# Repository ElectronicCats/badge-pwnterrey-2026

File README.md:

# Badge PWNTerrey

El **El Badge de Pwnterrey** es un dispositivo de hardware abierto y portátil diseñado para la auditoría de redes inalámbricas y seguridad de radiofrecuencia (WiFi, Bluetooth y NFC). Esta versión utiliza el potente y nuevo chip **ESP32-C5 (Arquitectura RISC-V)**, configurada específicamente para operar en modo **"Headless"** (sin pantalla), permitiendo la interacción total mediante consola serie (CLI) e integrando sensores y emuladores como NFC y GPS externo.

***

## 🚀 Características Principales

### 📶 Conectividad Inalámbrica Avanzada
- **Procesador ESP32-C5**: Chip de doble banda Wi-Fi 6 (2.4 GHz y 5 GHz) y Bluetooth 5 (LE) integrado.
- **Auditoría WiFi**: Soporte para escaneo de APs, rastreo de estaciones, sniffing de paquetes, inyección de tramas de desautenticación, spam de beacons y captura de handshakes.
- **Bluetooth (BLE)**: Capacidad para ejecutar ataques de spam BLE (`blespam`).

### 🏷️ Periféricos y Sensores Integrados
- **Emulador NFC (NT3H2111)**: Chip NTAG I2C 2k que permite actuar en **Modo Tarjeta**. El ESP32 emula una etiqueta pasiva para transferir datos NDEF (URLs, textos, vCards, redes WiFi) a teléfonos móviles o Flipper Zero.
- **Receptor GPS**: Interfaz serial dedicada para capturar coordenadas geográficas en tiempo real (Wardriving) y parsear sentencias NMEA.

### ⚙️ Optimización Headless (Sin Pantalla)
- **Bajo Consumo**: Al eliminar pantallas TFT/OLED y botones físicos, se reduce la huella energética y se maximiza la estabilidad.
- **Control Serial Total**: Una robusta interfaz de comandos (CLI) que permite controlar el 100% de las funciones del dispositivo.

***

## 📋 Especificaciones Técnicas

| Componente | Especificación |
| :--- | :--- |
| **Microcontrolador** | ESP32-C5 ECO1 (Arquitectura RISC-V de 32 bits) |
| **Wi-Fi** | Doble banda 2.4 GHz y 5 GHz (Wi-Fi 6 / 802.11ax) |
| **Bluetooth** | Bluetooth 5.0 (Low Energy - LE) |
| **NFC** | Chip **NT3H2111 (NTAG I2C 2k)** emulador de etiqueta pasiva |
| **GPS** | Interfaz serie dedicada para receptor GPS externo (UART1) |
| **Interfaz de Control**| CLI por Puerto Serie USB (115200 baudios) |
| **Estabilidad** | PSRAM desactivada, Flash configurada a 40MHz |

***

## 🔌 Interfaces y Pinout del ESP32-C5

El circuito integrado ESP32-C5 en su configuración Marauder utiliza los siguientes pines clave:

### 🌐 Conexión NFC (I2C)
El chip NTAG NT3H2111 está conectado a través del bus I2C:
- **SDA**: GPIO 2 (Pin 4)
- **SCL**: GPIO 3 (Pin 5)
- **Field Detect (FD)**: GPIO 6 (Pin 8) *(Detecta cuando un lector NFC externo energiza el campo inductivo)*

### 🛰️ Conexión GPS (UART1)
La comunicación con el módulo GPS se realiza mediante los pines:
- **GPS TX (MCU)**: GPIO 4 *(Hacia el pin RX del GPS)*
- **GPS RX (MCU)**: GPIO 5 *(Desde el pin TX del GPS)*
- **GPS ON/Power**: GPIO 7 *(Control de encendido del módulo GPS)*

***

## ⚡ Primeros Pasos

### 1. Alimentación y Conexión
Puedes alimentar y controlar tu adaptador de dos formas:
- **Conexión Directa USB**: Conéctalo a tu computadora usando un cable USB-C. El puerto creará un puerto COM serial.
- **Integración con Flipper Zero**: Conectado como un Addon GPIO al Flipper Zero, alimentado directamente desde los pines de 3.3V/5V del Flipper y controlado desde su aplicación de terminal.

### 2. Abrir la Terminal Serial
El dispositivo se comunica a **115200 baudios**, sin control de flujo (8N1).

#### 🐧 Linux / macOS
Usa el comando `screen` o `minicom`. Primero identifica el puerto (`/dev/ttyUSBX` o `/dev/ttyACM0`):
```bash
# Con screen (para salir: Ctrl+A, luego K)
screen /dev/ttyUSB0 115200

# Con minicom
sudo minicom -b 115200 -D /dev/ttyUSB0
```

#### 🪟 Windows
Usa clientes como **PuTTY** o **TeraTerm**:
- **Puerto**: COMx (Ver en administrador de dispositivos)
- **Baudrate**: 115200
- **Data bits**: 8
- **Parity**: None
- **Stop bits**: 1
- **Flow control**: None

***

## 🏷️ Control del Emulador NFC

El módulo NFC funciona exclusivamente en **modo emulación de etiqueta (Tag)**. No es un lector; actúa como una tarjeta inteligente pasiva que almacena registros NDEF.

### 🔍 Diagnóstico e Información
- **Escanear bus NFC**:
  ```bash
  nfc scan
  ```
  Realiza un escaneo de hardware (discovery) en los pares de pines del bus I2C para verificar la dirección del chip (`0x55` o `0x2A`).
- **Leer contenido actual de la etiqueta**:
  ```bash
  nfc read
  ```
  Muestra en hexadecimal y ASCII los bloques del 1 al 8 grabados en la memoria del chip NFC.

### ✍️ Escritura de Registros NDEF
Puedes programar el emulador NFC para inyectar diferentes cargas útiles:

- **🔗 Enlace Web (URL)**:
  ```bash
  nfc -u https://electroniccats.com
  ```
- **📝 Texto Plano**:
  ```bash
  nfc -t "Hola Hackers del ESP32-C5"
  ```
- **📇 Tarjeta de Contacto (vCard)**:
  ```bash
  nfc -v "Nombre,Telefono,Email"
  # Ejemplo:
  nfc -v "Electronic Cats,5551234567,info@electroniccats.com"
  ```
- **📶 Credenciales de Red WiFi**:
  ```bash
  nfc -w "SSID,Password,Autenticacion"
  # Ejemplo:
  nfc -w "MiRedSegura,Clave1234,WPA2"
  ```

Una vez ejecutado el comando con éxito, cualquier dispositivo móvil o lector NFC (como un Flipper Zero) que se acerque al sensor detectará la etiqueta y ejecutará la acción (abrir el link, importar el contacto o conectarse al WiFi).

***

## ⚙️ Configuración y Compilación de Firmware

Si deseas compilar o realizar modificaciones en el firmware, debes seguir estas recomendaciones específicas para el hardware ESP32-C5:

Clonar el [repositorio](https://github.com/ElectronicCats/badge-pwnterrey-2026)

### 🛠️ Configuración en configs.h
Asegúrate de que en el archivo [configs.h](file:///run/media/omaro/8C96D9BF96D9AA4A/ESP32Marauder/ESP32Marauder/esp32_marauder/configs.h) la definición activa para la placa sea:
```cpp
#define MARAUDER_FLIPPER_C5
```
Esta definición configurará automáticamente la ausencia de pantalla (`TFT_CS -1`), habilitará `HAS_BT`, `HAS_GPS` y `HAS_NFC` con sus respectivos mapeos de pines.

### ⚠️ Parámetros de Compilación en Arduino IDE
Debido al estado actual del soporte del chip, aplica las siguientes configuraciones de carga:
- **Placa**: ESP32C5 Dev Module
- **Arquitectura**: RISC-V (Compiler optimization)
- **Flash Frequency**: **40MHz** (Recomendado para máxima estabilidad)
- **Partition Scheme**: Minimal SPIFFS / No OTA (Para maximizar el espacio de programa y SPIFFS)
- **PSRAM**: Desactivada (Disabled)
- **Modo de Carga**: Inserte el dispositivo en modo Bootloader manteniendo presionado el botón Boot mientras conecta el USB si no es detectado automáticamente.

***

## ⌨️ Consola de Comandos Completa (CLI Reference)

A continuación se detalla la lista de comandos disponibles en el intérprete de comandos serial:

### 🛠️ Comandos de Administración

| Comando | Sintaxis | Descripción |
| :--- | :--- | :--- |
| `help` | `help` | Muestra la lista de comandos con su formato de ayuda. |
| `info` | `info` | Muestra información del sistema, compilación y hardware. |
| `reboot` | `reboot` | Reinicia el microcontrolador. |
| `channel` | `channel [-s <canal>]` | Muestra o cambia el canal WiFi activo. |
| `settings` | `settings [-s <setting> <enable/disable>]` | Muestra, modifica o reinicia (`-r`) los ajustes internos. |
| `spiffs` | `spiffs [ls / read <file> / rm <file> / format]`| Administra la memoria flash interna (SPIFFS). |
| `led` | `led -s <hex color> / -p <rainbow>` | Cambia el color del led de estado. |

### 📶 Auditoría WiFi (Sniffing & Scanning)

| Comando | Sintaxis | Descripción |
| :--- | :--- | :--- |
| `scanap` | `scanap` | Busca puntos de acceso (APs) inalámbricos cercanos. |
| `scansta` | `scansta` | Busca estaciones y clientes conectados. |
| `stopscan` | `stopscan` | Detiene inmediatamente cualquier escaneo en curso. |
| `list` | `list [-a / -s / -c / -t]` | Muestra listas cargadas (`-a` APs, `-s` SSIDs, `-c` Clientes). |
| `select` | `select -a/-s/-c <indices>` | Selecciona elementos por índice para interactuar. |
| `clearlist`| `clearlist -a/-c/-s` | Limpia los registros de la memoria RAM. |
| `ssid` | `ssid -a [-g <count> / -n <name>]` | Agrega SSIDs a la lista (`-g` aleatorios, `-n` específicos). |
| `sniffraw` | `sniffraw` | Captura y vuelca todos los paquetes raw recibidos. |
| `sniffbeacon`| `sniffbeacon` | Captura tramas beacon. |
| `sniffprobe`| `sniffprobe` | Captura peticiones probe request de clientes. |
| `sniffpwn` | `sniffpwn` | Sniffer enfocado en capturas de handshakes WPA. |
| `sniffpmkid`| `sniffpmkid [-c <channel>]` | Captura asociaciones PMKID para auditoría WPA2. |

### 💥 Comandos de Ataque WiFi y Bluetooth

| Comando | Sintaxis | Descripción |
| :--- | :--- | :--- |
| `attack` | `attack -t <deauth/beacon/probe/rickroll>` | Inicia ataque de desautenticación, spam de beacons, etc. |
| `blespam` | `blespam -t <apple/google/samsung/windows/all>`| Inicia campañas de spam publicitario Bluetooth BLE. |
| `wardrive` | `wardrive [-s]` | Inicia el modo Wardriving clásico sincronizado con GPS. |

***

## ⚠️ Advertencia de Seguridad

Esta herramienta ha sido diseñada exclusivamente para **fines educativos, pruebas de penetración ética y auditorías de seguridad autorizadas**. 

El uso de este dispositivo para interferir, interceptar o atacar redes e infraestructura ajena sin el consentimiento previo por escrito del propietario es **estrictamente ilegal**. Los desarrolladores y colaboradores no se hacen responsables del uso indebido de esta herramienta ni de los daños que este pueda causar.

## 📖 Documentación Adicional

- [Marauder App](https://github.com/ElectronicCats/marauder-ui-android-app)
- [Marauder UI Pro](https://github.com/ElectronicCats/marauder-ui-pro)
- [Firmware](https://github.com/ElectronicCats/pwnterrey-2026_Firmware)

## 🤝 Contribuciones

Este es un proyecto de hardware abierto. Las contribuciones son bienvenidas:

1. Haz un fork del repositorio.
2. Crea una nueva rama para tu feature (`git checkout -b feature/AmazingFeature`)
3. Haz commit de tus cambios (`git commit -m 'Add some AmazingFeature'`)
4. Haz push a tu rama (`git push origin feature/AmazingFeature`)
5. Abre un Pull Request

## 📝 Licencia

Este proyecto es de hardware abierto. Consulta los archivos de licencia para más detalles.

## 🏢 Electronic Cats

Desarollado con ❤️ por [Electronic Cats](https://www.electroniccats.com/)

Electronic Cats invierte tiempo y recursos en proporcionar este diseño de hardware abierto.
Por favor, apoya a Electronic Cats y al hardware abierto comprando productos de Electronic Cats.

## 📞 Contacto y soporte 

- **Website**: [https://www.electroniccats.com/](https://www.electroniccats.com/)
- **GitHub**: [ElectronicCats](https://github.com/ElectronicCats)
- **Issues**: Usa la sección de Issues en GitHub para reportar problemas o sugerir mejoras

## 🙏 Agradecimientos

Gracias a toda la comunidad de hardware abierto y a todas las personas que hacen posibles proyectos como este.

## 🤝 Credits & Ecosystem
- **Hardware & Support**: [Electronic Cats](https://electroniccats.com) 😼
- **Original Firmware**: [justcallmekoko](https://github.com/justcallmekoko)
- **UI Maintenance**: [michelangelomo](https://github.com/michelangelomo) & [Mikystars](https://github.com/Mikystars)

---
*Developed for the Offensive Security community.* 💀

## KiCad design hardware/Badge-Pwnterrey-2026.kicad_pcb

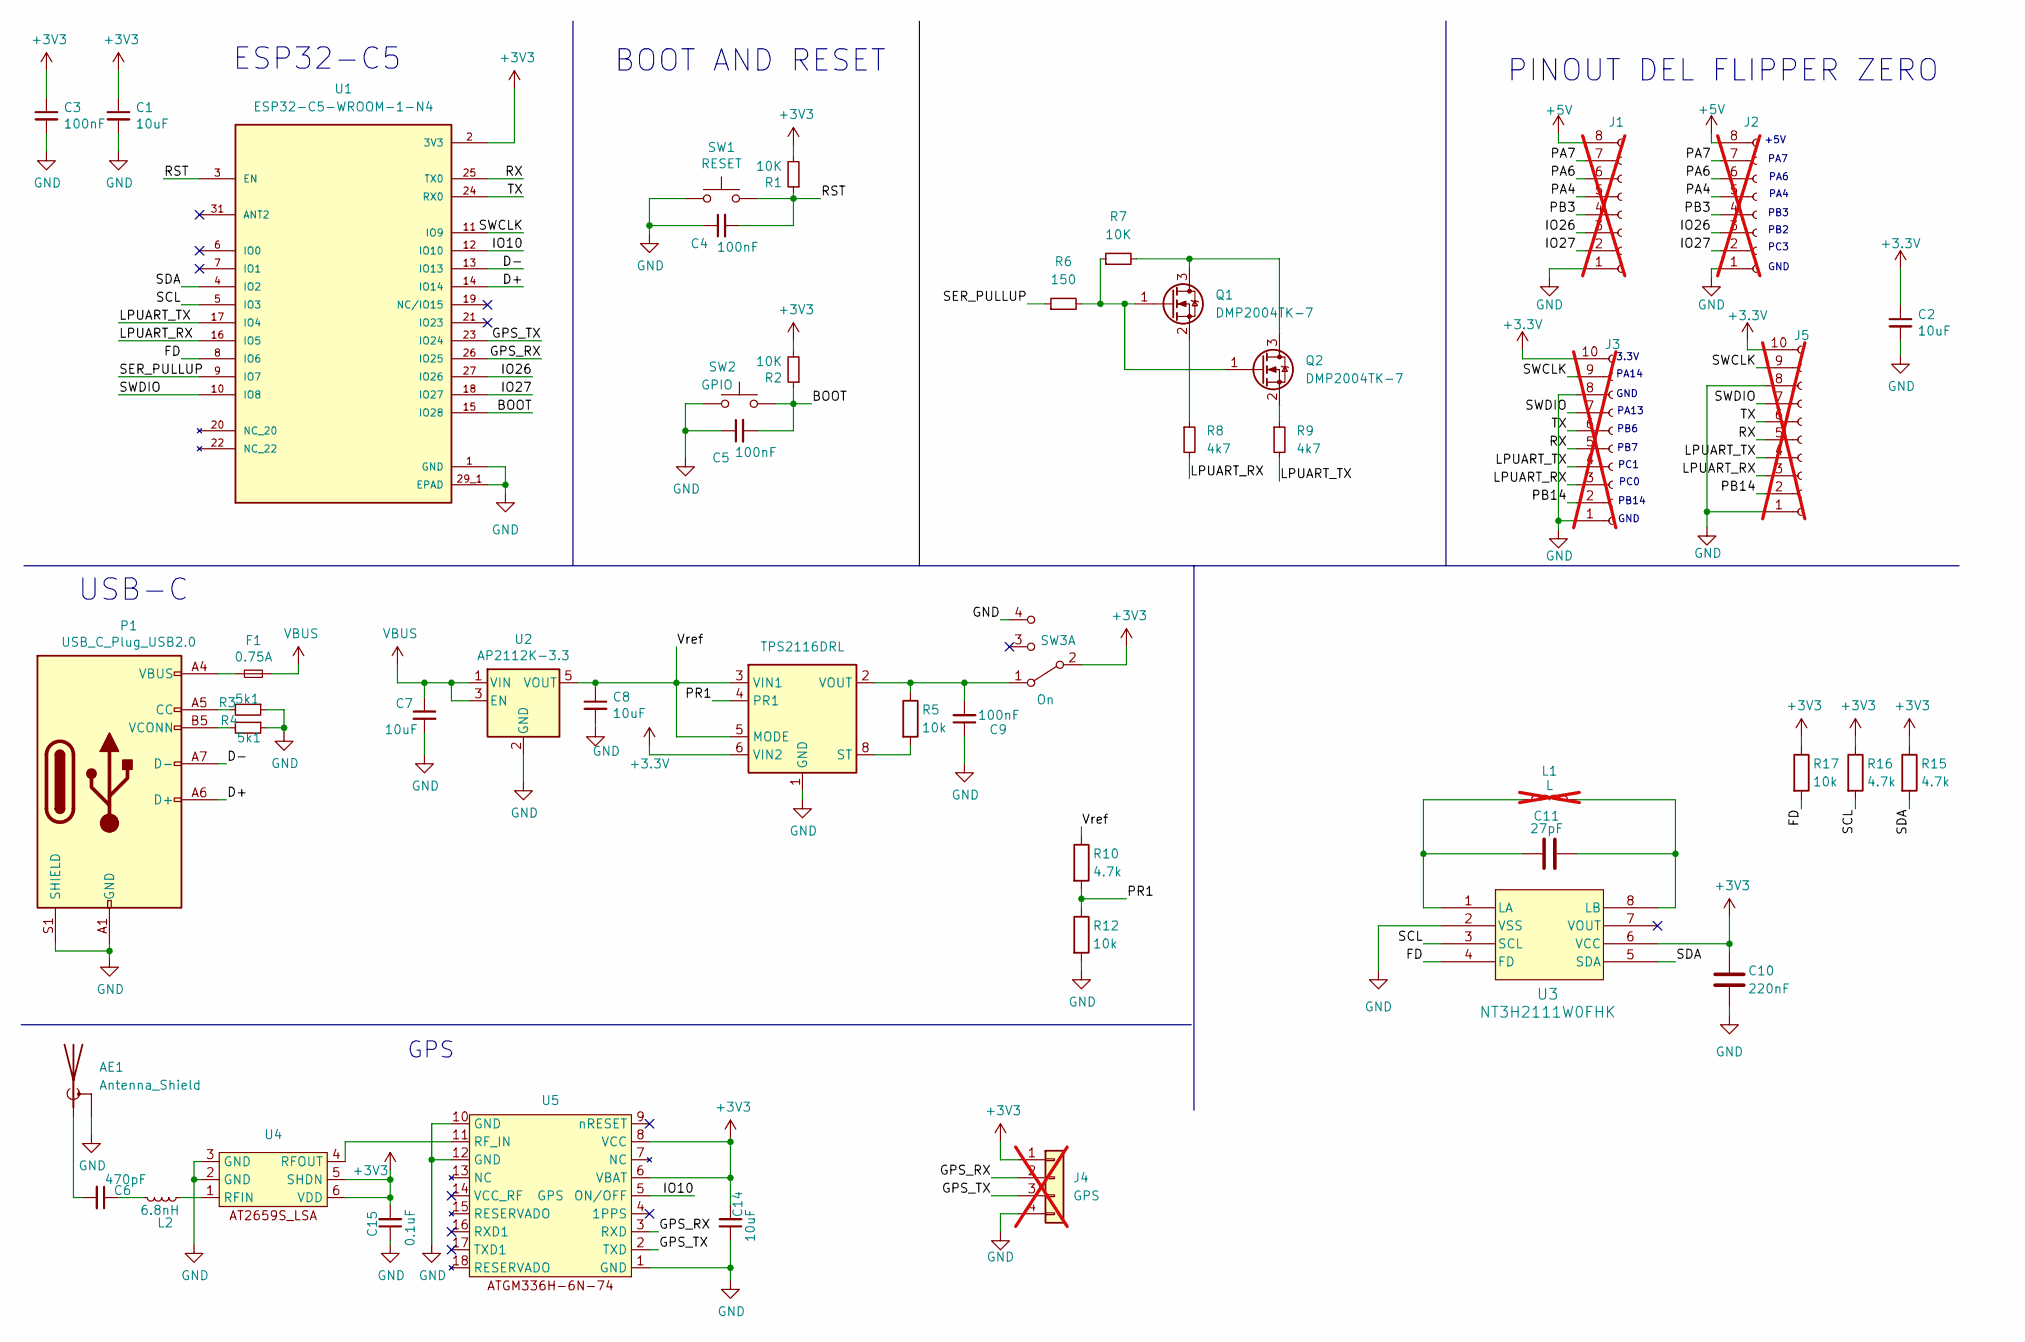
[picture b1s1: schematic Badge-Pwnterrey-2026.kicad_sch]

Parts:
AE1: Antenna_Shield; U.FL_Molex_MCRF_73412-0110_Vertical; LCSC# C7426714
C1, C2, C7, C8, C14: 10uF; C_0603_1608Metric; LCSC# C85713
C3, C4, C5, C9: 100nF; C_0603_1608Metric; LCSC# C597251
C6: 470pF; C_0603_1608Metric; LCSC# C1620
C10: 220nF; C_0603_1608Metric; LCSC# C344195
C11: 27pF; C_0603_1608Metric; LCSC# C107045
C15: 0.1uF; C_0603_1608Metric; LCSC# C478888
F1: 0.75A; Fuse_0603_1608Metric; LCSC# C182438
J1, J2: Conn_01x08_Socket; PinHeader_1x08_P2.54mm_Vertical; LCSC# C49326132; not fitted
J3, J5: Conn_01x10_Socket; PinHeader_1x10_P2.54mm_Vertical; LCSC# C49326134; not fitted
J4: GPS; PinHeader_1x04_P2.54mm_Vertical; not fitted
L1: L; Untitled; not fitted
L2: 6.8nH; L_0603_1608Metric_Pad1.05x0.95mm_HandSolder; LCSC# C49447
P1: USB_C_Plug_USB2.0; C393939; LCSC# C2760486
Q1, Q2: DMP2004TK-7; SOT-523
R1, R2, R7: 10K; R_0603_1608Metric; LCSC# C217281
R3, R4: 5k1; R_0603_1608Metric; LCSC# C156350
R5, R12, R17: 10k; R_0603_1608Metric; LCSC# C2930027
R6: 150; R_0603_1608Metric; LCSC# C2692872
R8, R9: 4k7; R_0603_1608Metric; LCSC# C394547
R10, R15, R16: 4.7k; R_0603_1608Metric; LCSC# C2907034
SW1: RESET; SW_SPST_TL3342; LCSC# C2886897
SW2: GPIO; SW_SPST_TL3342; LCSC# C2886897
SW3: On; MSK12C02; LCSC# C431540
U1: ESP32-C5-WROOM-1-N4; esp32c5wroom1n4
U2: AP2112K-3.3; SOT-23-5; LCSC# C150742
U3: NT3H2111W0FHK; XQFN8_NT3H2111_NXP-L; LCSC# C710403
U4: LNA; AT2659S-LSA; LCSC# C883443
U5: GPS; GPSM-SMD_ATGM336H; LCSC# C5804601
U7: TPS2116DRL; SOT-583-8; LCSC# C3235557

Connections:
+3.3V: C2.1, J3.10 (Pin_1), J5.10 (Pin_1), U7.6 (VIN2)
+3V3: C1.1, C3.1, C10.1, C14.2, C15.2, J4.1, R1.2, R2.2, R15.1, R16.1, R17.1, SW3.2 (B), U1.2 (3V3), U3.6 (VCC), U4.5 (SHDN), U4.6 (VDD), U5.6 (VBAT), U5.8 (VCC)
+5V: J1.8 (Pin_1), J2.8 (Pin_1)
/BOOT: C5.2, R2.1, SW2.2, U1.15 (IO28)
/D+: P1.A6 (D+), U1.14 (IO14)
/D-: P1.A7 (D-), U1.13 (IO13)
/FD: R17.2, U1.8 (IO6), U3.4 (FD)
/GPS_RX: J4.2, U1.26 (IO25), U5.3 (RXD)
/GPS_TX: J4.3, U1.23 (IO24), U5.2 (TXD)
/IO10: U1.12 (IO10), U5.5 (ON/OFF)
/IO26: J1.3 (Pin_6), J2.3 (Pin_6), U1.27 (IO26)
/IO27: J1.2 (Pin_7), J2.2 (Pin_7), U1.18 (IO27)
/LPUART_RX: J3.3 (Pin_8), J5.3 (Pin_8), R8.2, U1.16 (IO5)
/LPUART_TX: J3.4 (Pin_7), J5.4 (Pin_7), R9.2, U1.17 (IO4)
/PA4: J1.5 (Pin_4), J2.5 (Pin_4)
/PA6: J1.6 (Pin_3), J2.6 (Pin_3)
/PA7: J1.7 (Pin_2), J2.7 (Pin_2)
/PB3: J1.4 (Pin_5), J2.4 (Pin_5)
/PB14: J3.2 (Pin_9), J5.2 (Pin_9)
/PR1: R10.2, R12.1, U7.4 (PR1)
/RST: C4.2, R1.1, SW1.2, U1.3 (EN)
/RX: J3.5 (Pin_6), J5.5 (Pin_6), U1.25 (TX0)
/SCL: R16.2, U1.5 (IO3), U3.3 (SCL)
/SDA: R15.2, U1.4 (IO2), U3.5 (SDA)
/SER_PULLUP: R6.1, U1.9 (IO7)
/SWCLK: J3.9 (Pin_2), J5.9 (Pin_2), U1.11 (IO9)
/SWDIO: J3.7 (Pin_4), J5.7 (Pin_4), U1.10 (IO8)
/TX: J3.6 (Pin_5), J5.6 (Pin_5), U1.24 (RX0)
/Vref: C8.1, R10.1, U2.5 (VOUT), U7.3 (VIN1), U7.5 (MODE)
GND: AE1.2 (Shield), C1.2, C2.2, C3.2, C4.1, C5.1, C7.2, C8.2, C9.1, C10.2, C14.1, C15.1, J1.1 (Pin_8), J2.1 (Pin_8), J3.1 (Pin_10), J3.8 (Pin_3), J4.4, J5.1 (Pin_10), J5.8 (Pin_3), P1.A1 (GND), P1.A12 (GND), P1.B1 (GND), P1.B12 (GND), P1.S1 (SHIELD), R3.1, R4.1, R12.2, SW1.1, SW2.1, SW3.4 (C), U1.1 (GND), U1.28 (GND), U1.29, U1.29_1 (EPAD), U1.29_2 (EPAD), U1.29_3 (EPAD), U1.29_4 (EPAD), U1.29_5 (EPAD), U1.29_6 (EPAD), U1.29_7 (EPAD), U1.29_8 (EPAD), U1.29_9 (EPAD), U1.30 (GND), U1.31 (ANT2), U1.32 (GND), U1.33, U1.34, U1.35, U1.36, U1.37, U2.2 (GND), U3.2 (VSS), U4.2 (GND), U4.3 (GND), U5.1 (GND), U5.10 (GND), U5.12 (GND), U7.1 (GND)
unnamed: AE1.1 (A), C6.2
unnamed: C6.1, L2.2
unnamed: F1.1, P1.A4 (VBUS), P1.A9 (VBUS), P1.B4 (VBUS), P1.B9 (VBUS)
unnamed: P1.A5 (CC), R3.2
unnamed: P1.B5 (VCONN), R4.2
unnamed: Q1.3 (D), Q2.3 (D), R7.2
unnamed: Q1.1 (G), Q2.1 (G), R6.2, R7.1
unnamed: Q1.2 (S), R8.1
unnamed: Q2.2 (S), R9.1
unnamed: C9.2, R5.1, SW3.1 (A), U7.2 (VOUT), U7.7 (VOUT)
unnamed: C11.1, L1.1, U3.1 (LA)
unnamed: C11.2, L1.2, U3.8 (LB)
unnamed: L2.1, U4.1 (RFIN)
unnamed: U4.4 (RFOUT), U5.11 (RF_IN)
unnamed: R5.2, U7.8 (ST)
VBUS: C7.1, F1.2, U2.1 (VIN), U2.3 (EN)

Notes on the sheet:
PB2
GPS
PA14
PC1
PB6
PINOUT DEL FLIPPER ZERO
PA13
GND
ESP32-C5
PB14
USB-C
PB7
3.3V
PC0
+5V
PC3
PA7
PA6
PB3
BOOT AND RESET
PA4

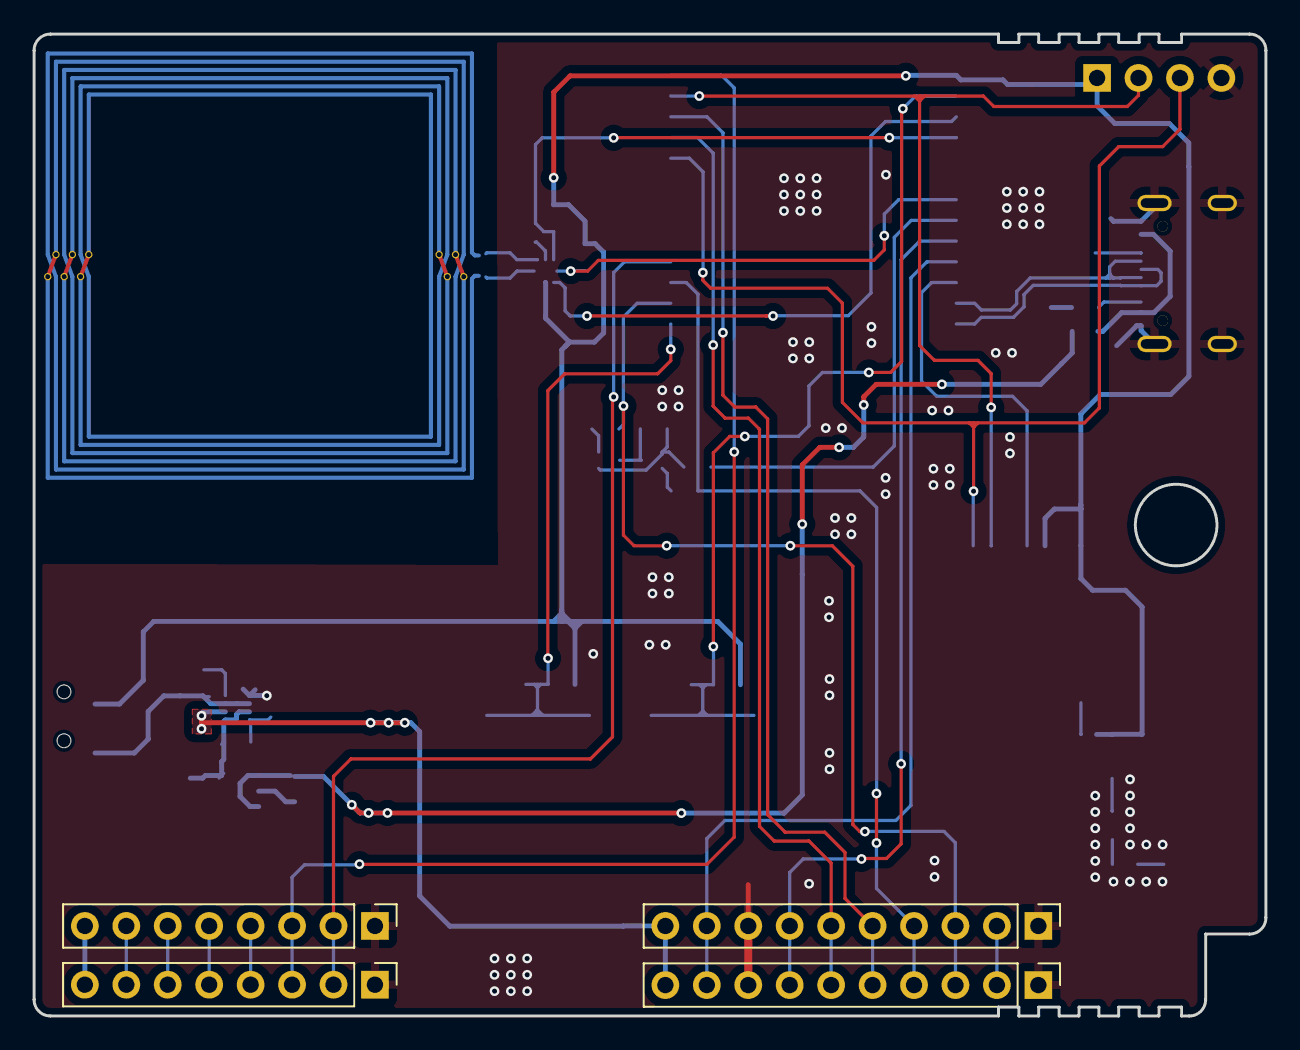
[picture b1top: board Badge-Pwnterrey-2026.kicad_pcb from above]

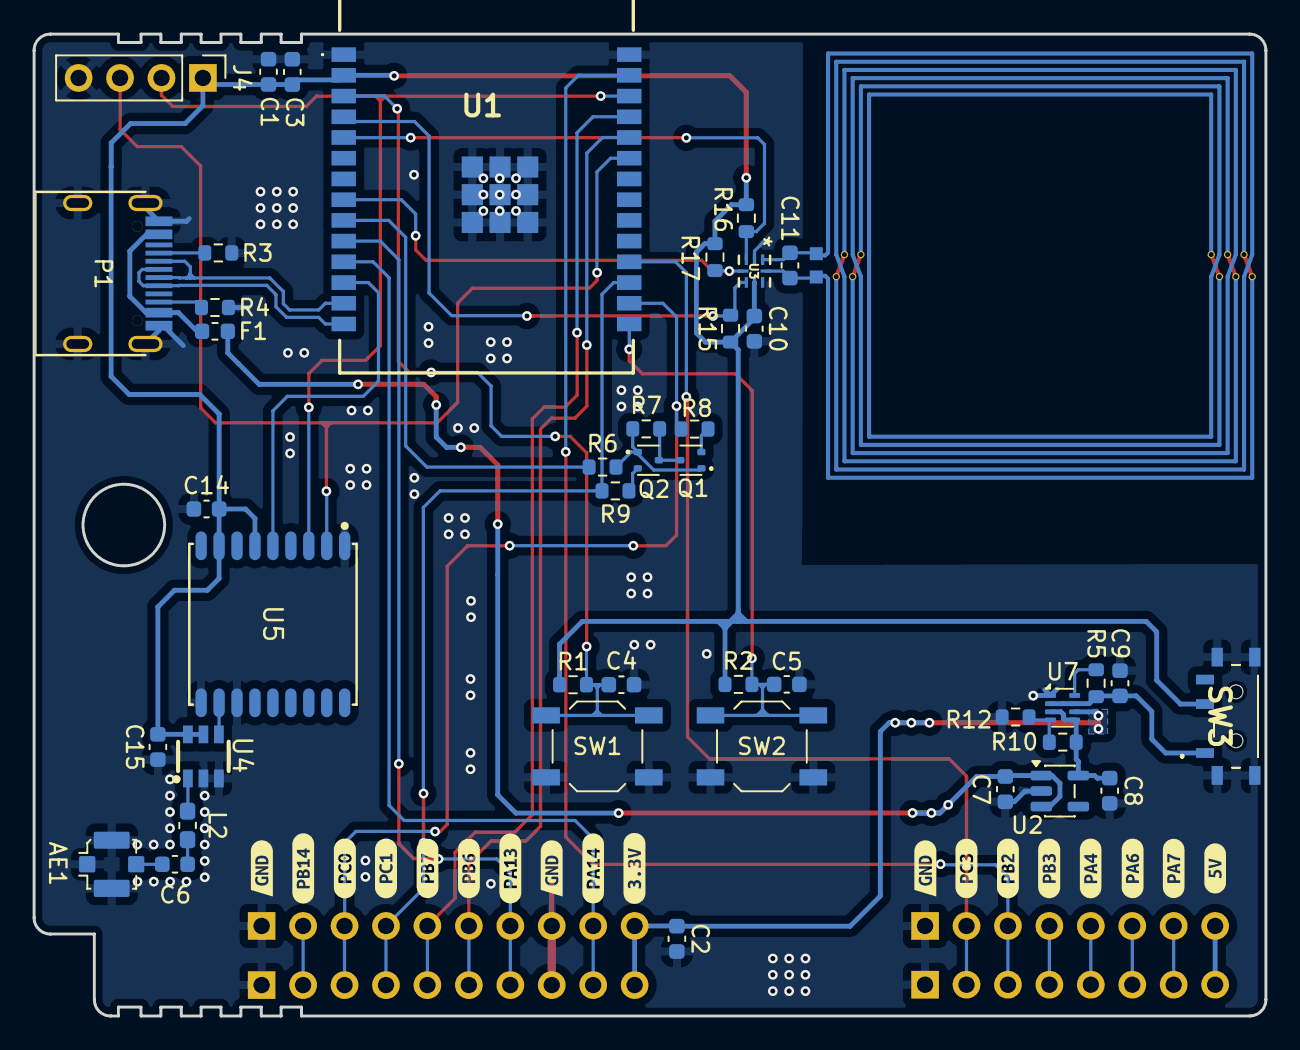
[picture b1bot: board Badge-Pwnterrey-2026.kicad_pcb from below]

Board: 2 copper layers, 75.5 x 60.2 mm, 66 parts (61 on the bottom side), 46 nets.

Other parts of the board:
kibuzzard-64E4E5CE: G***; kibuzzard-64E4E5CE
kibuzzard-648B91CB: G***; kibuzzard-648B91CB
kibuzzard-648B91E6: G***; kibuzzard-648B91E6
kibuzzard-648B91FC: G***; kibuzzard-648B91FC
kibuzzard-648B93B1: G***; kibuzzard-648B93B1
kibuzzard-648B93BF: G***; kibuzzard-648B93BF
kibuzzard-648B93D2: G***; kibuzzard-648B93D2
kibuzzard-648B93E0: G***; kibuzzard-648B93E0
kibuzzard-648B93EF: G***; kibuzzard-648B93EF
kibuzzard-648B921B: G***; kibuzzard-648B921B
kibuzzard-648B922F: G***; kibuzzard-648B922F
kibuzzard-648B923F: G***; kibuzzard-648B923F
kibuzzard-648B9401: G***; kibuzzard-648B9401
kibuzzard-648B9410: G***; kibuzzard-648B9410
kibuzzard-6488EEAF, kibuzzard-6488EEAF#2, kibuzzard-6488EEAF#3: G***; kibuzzard-6488EEAF
kibuzzard-6488F75A: G***; kibuzzard-6488F75A

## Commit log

2026-03-03 feat(Hw):Init_Schematic
2026-03-11 feat(Hw):Init_Floorplan
2026-03-20 feat(Hw):Update_Schematic_And_Init_Route
2026-03-23 feat(Hw):Update_Labels
2026-03-24 feat(Hw):Update_PCB
2026-03-24 feat(Hw):Update_Schematic_And_Route
2026-03-27 feat(hw):Added_TPS2116DRL
2026-03-30 feat(Hw):Update_BOM
2026-04-08 feat(Hw):GPS_Pins_Added
2026-05-04 feat: Add CERN Open Hardware Licence v1.2
    This document outlines the terms and conditions of the CERN Open Hardware Licence v1.2, including definitions, applicability, and rights for Licensees and Licensors.
2026-05-04 Update README with UI and firmware links
    Added links for UI and firmware resources related to badges.
2026-05-25 Revise README for ESP32 Marauder C5 specifications
    Updated README to reflect new project details and features for ESP32 Marauder C5.
2026-05-25 Change project title to 'Badge PWNTerrey'
    Updated project title and description in README.md.
2026-05-25 Remove Bluetooth commands from README
    Removed Bluetooth sniffing and wardriving commands from the README.
2026-05-27 Docs: Revise README for Badge Pwnterrey and cloning instructions
    Updated the project name and added repository link for cloning.
2026-05-27 docs: Enhance README with documentation and contribution details
    Added additional documentation, contribution guidelines, license information, and acknowledgments.
